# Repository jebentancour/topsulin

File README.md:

# Topsulin

## Software

### BLE Services and Characteristics

|GATT Services |GATT Characteristics            |Description                              |
|--------------|--------------------------------|-----------------------------------------|
|**Glucose**   |0x1808                          |Servicio estándar para glucómetros       |
|0x2A18        |**Glucose Measurement**         |Valores de glucemia                      |
|0x2A34        |**Glucose Measurement Context** |Información adicional (CHO e insulina)   |
|0x2A51        |**Glucose Feature**             |Información sobre features soportadas    |
|0x2A52        |**Record Access Control Point** |Punto de control de acceso del registro  |
|**Topsulin**  |0xF65D                          |Servicio específico de Topsulin          |
|0xF65E        |**Configuration**               |Configuración de preferencias de usuario |
|0xF65F        |**Name**                        |Nombre para mostrar                      |
|0xF660        |**Time**                        |Fecha y hora                             |
|0xF661        |**Calculator**                  |Parámetros para el calculador de bolos   |
|0xF662        |**Insulin**                     |Tipo, capacidad y cantidad restante      |
|0xF663        |**Device**                      |Información sobre el dispositivo         |

Base UUID para Topsulin Services y Characteristics 0x3419-XXXX-1505-31A7-EC4D-449B-0752-1104

#### Glucose Service

Según el servicio estándar [Glucose Service Specification](https://www.bluetooth.com/specifications/gatt/viewer?attributeXmlFile=org.bluetooth.service.glucose.xml)

Definimos que 1 U de insulina se representa como 10 ml.

```c
/**@brief Glucose feature */
#define BLE_GLS_FEATURE_LOW_BATT                       0x0001  /**< Low Battery Detection During Measurement Supported */
#define BLE_GLS_FEATURE_MALFUNC                        0x0002  /**< Sensor Malfunction Detection Supported */
#define BLE_GLS_FEATURE_SAMPLE_SIZE                    0x0004  /**< Sensor Sample Size Supported */
#define BLE_GLS_FEATURE_INSERT_ERR                     0x0008  /**< Sensor Strip Insertion Error Detection Supported */
#define BLE_GLS_FEATURE_TYPE_ERR                       0x0010  /**< Sensor Strip Type Error Detection Supported */
#define BLE_GLS_FEATURE_RES_HIGH_LOW                   0x0020  /**< Sensor Result High-Low Detection Supported */
#define BLE_GLS_FEATURE_TEMP_HIGH_LOW                  0x0040  /**< Sensor Temperature High-Low Detection Supported */
#define BLE_GLS_FEATURE_READ_INT                       0x0080  /**< Sensor Read Interrupt Detection Supported */
#define BLE_GLS_FEATURE_GENERAL_FAULT                  0x0100  /**< General Device Fault Supported */
#define BLE_GLS_FEATURE_TIME_FAULT                     0x0200  /**< Time Fault Supported */
#define BLE_GLS_FEATURE_MULTI_BOND                     0x0400  /**< Multiple Bond Supported */

/**@brief Glucose measurement flags */
#define BLE_GLS_MEAS_FLAG_TIME_OFFSET                  0x01    /**< Time Offset Present */
#define BLE_GLS_MEAS_FLAG_CONC_TYPE_LOC                0x02    /**< Glucose Concentration, Type, and Sample Location Present */
#define BLE_GLS_MEAS_FLAG_UNITS_KG_L                   0x00    /**< Glucose Concentration Units kg/L */
#define BLE_GLS_MEAS_FLAG_UNITS_MOL_L                  0x04    /**< Glucose Concentration Units mol/L */
#define BLE_GLS_MEAS_FLAG_SENSOR_STATUS                0x08    /**< Sensor Status Annunciation Present */
#define BLE_GLS_MEAS_FLAG_CONTEXT_INFO                 0x10    /**< Context Information Follows */

/**@brief Glucose measurement type */
#define BLE_GLS_MEAS_TYPE_CAP_BLOOD                    1       /**< Capillary whole blood */
#define BLE_GLS_MEAS_TYPE_CAP_PLASMA                   2       /**< Capillary plasma */
#define BLE_GLS_MEAS_TYPE_VEN_BLOOD                    3       /**< Venous whole blood */
#define BLE_GLS_MEAS_TYPE_VEN_PLASMA                   4       /**< Venous plasma */
#define BLE_GLS_MEAS_TYPE_ART_BLOOD                    5       /**< Arterial whole blood */
#define BLE_GLS_MEAS_TYPE_ART_PLASMA                   6       /**< Arterial plasma */
#define BLE_GLS_MEAS_TYPE_UNDET_BLOOD                  7       /**< Undetermined whole blood */
#define BLE_GLS_MEAS_TYPE_UNDET_PLASMA                 8       /**< Undetermined plasma */
#define BLE_GLS_MEAS_TYPE_FLUID                        9       /**< Interstitial fluid (ISF) */
#define BLE_GLS_MEAS_TYPE_CONTROL                      10      /**< Control solution */

/**@brief Glucose measurement location */
#define BLE_GLS_MEAS_LOC_FINGER                        1       /**< Finger */
#define BLE_GLS_MEAS_LOC_AST                           2       /**< Alternate Site Test (AST) */
#define BLE_GLS_MEAS_LOC_EAR                           3       /**< Earlobe */
#define BLE_GLS_MEAS_LOC_CONTROL                       4       /**< Control solution */
#define BLE_GLS_MEAS_LOC_NOT_AVAIL                     15      /**< Sample Location value not available */

/**@brief Glucose sensor status annunciation */
#define BLE_GLS_MEAS_STATUS_BATT_LOW                   0x0001  /**< Device battery low at time of measurement */
#define BLE_GLS_MEAS_STATUS_SENSOR_FAULT               0x0002  /**< Sensor malfunction or faulting at time of measurement */
#define BLE_GLS_MEAS_STATUS_SAMPLE_SIZE                0x0004  /**< Sample size for blood or control solution insufficient at time of measurement */
#define BLE_GLS_MEAS_STATUS_STRIP_INSERT               0x0008  /**< Strip insertion error */
#define BLE_GLS_MEAS_STATUS_STRIP_TYPE                 0x0010  /**< Strip type incorrect for device */
#define BLE_GLS_MEAS_STATUS_RESULT_HIGH                0x0020  /**< Sensor result higher than the device can process */
#define BLE_GLS_MEAS_STATUS_RESULT_LOW                 0x0040  /**< Sensor result lower than the device can process */
#define BLE_GLS_MEAS_STATUS_TEMP_HIGH                  0x0080  /**< Sensor temperature too high for valid test/result at time of measurement */
#define BLE_GLS_MEAS_STATUS_TEMP_LOW                   0x0100  /**< Sensor temperature too low for valid test/result at time of measurement */
#define BLE_GLS_MEAS_STATUS_STRIP_PULL                 0x0200  /**< Sensor read interrupted because strip was pulled too soon at time of measurement */
#define BLE_GLS_MEAS_STATUS_GENERAL_FAULT              0x0400  /**< General device fault has occurred in the sensor */
#define BLE_GLS_MEAS_STATUS_TIME_FAULT                 0x0800  /**< Time fault has occurred in the sensor and time may be inaccurate */

/**@brief Glucose measurement context flags */
#define BLE_GLS_CONTEXT_FLAG_CARB                      0x01    /**< Carbohydrate id and carbohydrate present */
#define BLE_GLS_CONTEXT_FLAG_MEAL                      0x02    /**< Meal present */
#define BLE_GLS_CONTEXT_FLAG_TESTER                    0x04    /**< Tester-health present */
#define BLE_GLS_CONTEXT_FLAG_EXERCISE                  0x08    /**< Exercise duration and exercise intensity present */
#define BLE_GLS_CONTEXT_FLAG_MED                       0x10    /**< Medication ID and medication present */
#define BLE_GLS_CONTEXT_FLAG_MED_KG                    0x00    /**< Medication value units, kilograms */
#define BLE_GLS_CONTEXT_FLAG_MED_L                     0x20    /**< Medication value units, liters */
#define BLE_GLS_CONTEXT_FLAG_HBA1C                     0x40    /**< Hba1c present */
#define BLE_GLS_CONTEXT_FLAG_EXT                       0x80    /**< Extended flags present */

/**@brief Glucose measurement context carbohydrate ID */
#define BLE_GLS_CONTEXT_CARB_BREAKFAST                 1       /**< Breakfast */
#define BLE_GLS_CONTEXT_CARB_LUNCH                     2       /**< Lunch */
#define BLE_GLS_CONTEXT_CARB_DINNER                    3       /**< Dinner */
#define BLE_GLS_CONTEXT_CARB_SNACK                     4       /**< Snack */
#define BLE_GLS_CONTEXT_CARB_DRINK                     5       /**< Drink */
#define BLE_GLS_CONTEXT_CARB_SUPPER                    6       /**< Supper */
#define BLE_GLS_CONTEXT_CARB_BRUNCH                    7       /**< Brunch */

/**@brief Glucose measurement context meal */
#define BLE_GLS_CONTEXT_MEAL_PREPRANDIAL               1       /**< Preprandial (before meal) */
#define BLE_GLS_CONTEXT_MEAL_POSTPRANDIAL              2       /**< Postprandial (after meal) */
#define BLE_GLS_CONTEXT_MEAL_FASTING                   3       /**< Fasting */
#define BLE_GLS_CONTEXT_MEAL_CASUAL                    4       /**< Casual (snacks, drinks, etc.) */
#define BLE_GLS_CONTEXT_MEAL_BEDTIME                   5       /**< Bedtime */

/**@brief Glucose measurement context tester */
#define BLE_GLS_CONTEXT_TESTER_SELF                    1       /**< Self */
#define BLE_GLS_CONTEXT_TESTER_PRO                     2       /**< Health care professional */
#define BLE_GLS_CONTEXT_TESTER_LAB                     3       /**< Lab test */
#define BLE_GLS_CONTEXT_TESTER_NOT_AVAIL               15      /**< Tester value not available */

/**@brief Glucose measurement context health */
#define BLE_GLS_CONTEXT_HEALTH_MINOR                   1       /**< Minor health issues */
#define BLE_GLS_CONTEXT_HEALTH_MAJOR                   2       /**< Major health issues */
#define BLE_GLS_CONTEXT_HEALTH_MENSES                  3       /**< During menses */
#define BLE_GLS_CONTEXT_HEALTH_STRESS                  4       /**< Under stress */
#define BLE_GLS_CONTEXT_HEALTH_NONE                    5       /**< No health issues */
#define BLE_GLS_CONTEXT_HEALTH_NOT_AVAIL               15      /**< Health value not available */

/**@brief Glucose measurement context medication ID */
#define BLE_GLS_CONTEXT_MED_RAPID                      1       /**< Rapid acting insulin */
#define BLE_GLS_CONTEXT_MED_SHORT                      2       /**< Short acting insulin */
#define BLE_GLS_CONTEXT_MED_INTERMED                   3       /**< Intermediate acting insulin */
#define BLE_GLS_CONTEXT_MED_LONG                       4       /**< Long acting insulin */
#define BLE_GLS_CONTEXT_MED_PREMIX                     5       /**< Pre-mixed insulin */

/**@brief SFLOAT format (IEEE-11073 16-bit FLOAT, meaning 4 bits for exponent (base 10) and 12 bits mantissa) */
typedef struct
{
  int8_t exponent;                                             /**< Base 10 exponent, should be using only 4 bits */
  int16_t mantissa;                                            /**< Mantissa, should be using only 12 bits */
} sfloat_t;
```

Los enteros de 16 bits se codifican de manera que el byte más alto va primero. El número 250 en hexadecimal es 0x00FA, sin embargo en BLE se lee el byte 0xFA00.

El sfloat se usa para guardar un número con coma en 16 bits, los primeros 12 bits son la mantisa y los otros 4 el exponente.

```c
uint16_t encode_sfloat(sfloat_t sf)
{
    uint16_t dec;
    dec = ((sf.exponent << 12) & 0xF000) | ((sf.mantissa <<  0) & 0x0FFF);
    return dec;
}

sfloat_t decode_sfloat(uint16_t u)
{
    sfloat_t sf;
    sf.exponent = (u & 0xF000) >> 12;
    sf.mantissa = (u & 0x0FFF) >> 0;
    return sf;
}
```

#### Topsulin Service

[Characteristic Format Types](https://www.bluetooth.com/specifications/assigned-numbers/format-types)

|Characteristic                                      |Format |Value                              |Default                   |
|----------------------------------------------------|-------|-----------------------------------|--------------------------|
|**Configuration**                                   |       |                                   |                          |
|Registro de glucemia                                |bit0   |0 No, 1 Si                         |Si                        |
|Registro de insulina                                |bit1   |0 No, 1 Si                         |Si                        |
|Registro de CHO                                     |bit2   |0 No, 1 Si                         |Si                        |
|Invertir los colores de la pantalla                 |bit3   |0 Fondo blanco, 1 Fondo negro      |Fondo blanco              |
|Unidades de glucemia                                |bit4   |0 kg/L, 1 mol/L                    |kg/L                      |
|Calculador de bolo                                  |bit5   |0 Desactivado, 1 Activado          |Desactivado               |
|Orientación de pantalla                             |bit6   |0 Diestro, 1 Zurdo                 |Diestro                   |
|Unidades de CHO                                     |bit7   |0 CHO en g, 1 CHO en porciones     |CHO en g                  |
|Equivalencia entre gramos y porciones               |uint16 |Peso en g de una porción           |250 g                     |
|Incremento de CHO                                   |uint8  |Paso de ingreso de CHO en g        |5 g                       |
|Incremento de insulina                              |uint8  |Paso de ingreso de insulina x10    |10 (equivale a 1U)        |
|**Name**                                            |       |                                   |                          |
|Nombre para mostrar                                 |uint8  |String de largo máximo 20 UTF-8    |Glucosee                  |
|**Time**                                            |       |                                   |                          |
|Hora y fecha del dispositivo                        |time   |[Time Characteristic](https://www.bluetooth.com/specifications/gatt/viewer?attributeXmlFile=org.bluetooth.characteristic.date_time.xml) |01/01/19 12:00:00 |
|**Calculator**                                      |       |                                   |                          |
|Nivel bajo                                          |sfloat |Nivel de glucemia baja en kg/L     |90x10^-5 kg/L             |
|Nivel alto                                          |sfloat |Nivel de glucemia alta en kg/L     |150x10^-5 kg/L            |
|Sensibilidad                                        |uint16 |Cada cuántos CHO en g incremento insulina |15 g               |
|Corrección de hiperglucemia                         |sfloat |Cada cuántos kg/L de hiper incremento insulina |50x10^-5 kg/L |
|**Insulin**                                         |       |                                   |                          |
|Tipo de insulina                                    |uint8  |Medication ID from Glucose Service |BLE_GLS_CONTEXT_MED_RAPID |
|Capacidad de la lapicera                            |uint16 |U de insulina en una lapicera nueva|300 U                     |
|Capacidad restante de la lapicera                   |uint16 |U de insulina restantes            |120 U                     |
|Comienzo de acción                                  |uint16 |En minutos                         |30 m                      |
|Acción máxima                                       |uint16 |En minutos                         |120 m                     |
|Duración de la acción                               |uint16 |En minutos                         |360 m                     |
|**Device**                                          |       |                                   |                          |
|Firmware                                            |uint8  |Versión de firmware                |1                         |
|Serial Number                                       |uint16 |Número de serie                    |1                         |
|Battery                                             |uint16 |Voltaje de la batería en mV        |Cerca de 3300 mV          |

## Board

## Encoder

|nRF pin|Use  |
|-------|-----|
|01     |A    |
|00     |B    |
|30     |SW   |

## Display

|nRF pin|Use  |
|-------|-----|
|21     |MOSI |
|22     |CLK  |
|23     |CS   |
|24     |DC   |
|25     |RST  |
|28     |BUSY |

## SoC

SoC [nRF51822](https://www.nordicsemi.com/eng/nordic/download_resource/62726/14/39584073/13358) QFACA10 (256kB flash, 32 kB RAM)

[INFOCENTER](http://infocenter.nordicsemi.com)

|ID |Base address |Peripheral  |Instance    |Description                                  |Used by           |
|---|-------------|------------|------------|---------------------------------------------|------------------|
|0  |0x40000000   |POWER       |POWER       |Power Control.                               |SoftDevice        |
|0  |0x40000000   |CLOCK       |CLOCK       |Clock Control.                               |SoftDevice        |
|0  |0x40000000   |MPU         |MPU         |Memory Protection Unit.                      |SoftDevice        |
|1  |0x40001000   |RADIO       |RADIO       |2.4 GHz Radio.                               |SoftDevice        |
|2  |0x40002000   |UART        |UART0       |Universal Asynchronous Receiver/Transmitter. |                  |
|3  |0x40003000   |SPI         |SPI0        |SPI Master.                                  |EPD (SPI)         |
|3  |0x40003000   |TWI         |TWI0        |I2C compatible Two-Wire Interface 0.         |EPD (SPI)         |
|4  |0x40004000   |SPIS        |SPIS1       |SPI Slave.                                   |                  |
|4  |0x40004000   |SPI         |SPI1        |SPI Master.                                  |                  |
|4  |0x40004000   |TWI         |TWI1        |I2C compatible Two-Wire Interface 1.         |                  |
|6  |0x40006000   |GPIOTE      |GPIOTE      |GPIO Task and Events.                        |                  |
|7  |0x40007000   |ADC         |ADC         |Analog to Digital Converter.                 |Battery           |
|8  |0x40008000   |TIMER       |TIMER0      |Timer/Counter 0.                             |SoftDevice        |
|9  |0x40009000   |TIMER       |TIMER1      |Timer/Counter 1.                             |                  |
|10 |0x4000A000   |TIMER       |TIMER2      |Timer/Counter 2.                             |                  |
|11 |0x4000B000   |RTC         |RTC0        |Real Time Counter 0.                         |SoftDevice        |
|12 |0x4000C000   |TEMP        |TEMP        |Temperature Sensor.                          |SoftDevice        |
|13 |0x4000D000   |RNG         |RNG         |Random Number Generator.                     |SoftDevice        |
|14 |0x4000E000   |ECB         |ECB         |Crypto AES ECB.                              |SoftDevice        |
|15 |0x4000F000   |CCM         |CCM         |AES Crypto CCM.                              |SoftDevice        |
|15 |0x4000F000   |AAR         |AAR         |Accelerated Address Resolver.                |SoftDevice        |
|16 |0x40010000   |WDT         |WDT         |Watchdog Timer.                              |                  |
|17 |0x40011000   |RTC         |RTC1        |Real Time Counter 1.                         |Timer library     |
|18 |0x40012000   |QDEC        |QDEC        |Quadrature Decoder.                          |Encoder           |
|19 |0x40013000   |LPCOMP      |LPCOMP      |Low Power Comparator.                        |                  |
|20 |0x40014000   |SWI         |SWI0        |Software interrupt.                          |Timer library     |
|21 |0x40015000   |SWI         |SWI1        |Software interrupt.                          |SoftDevice        |
|22 |0x40016000   |SWI         |SWI2        |Software interrupt                           |SoftDevice        |
|23 |0x40017000   |SWI         |SWI3        |Software interrupt.                          |                  |
|24 |0x40018000   |SWI         |SWI4        |Software interrupt.                          |SoftDevice        |
|25 |0x40019000   |SWI         |SWI5        |Software interrupt.                          |SoftDevice        |
|30 |0x4001E000   |NVMC        |NVMC        |Non-Volatile Memory Controller.              |SoftDevice        |
|31 |0x4001F000   |PPI         |PPI         |Programmable Peripheral Interconnect.        |                  |
|NA |0x50000000   |GPIO        |GPIO        |General Purpose Input and Output.            |Gpio              |
|NA |0x10000000   |FICR        |FICR        |Factory Information Configuration Registers. |SoftDevice        |
|NA |0x10001000   |UICR        |UICR        |User Information Configuration Registers.    |SoftDevice        |

## EPD

[Image file to embedded C/C++ code](https://digole.com/tools/PicturetoC_Hex_converter.php)

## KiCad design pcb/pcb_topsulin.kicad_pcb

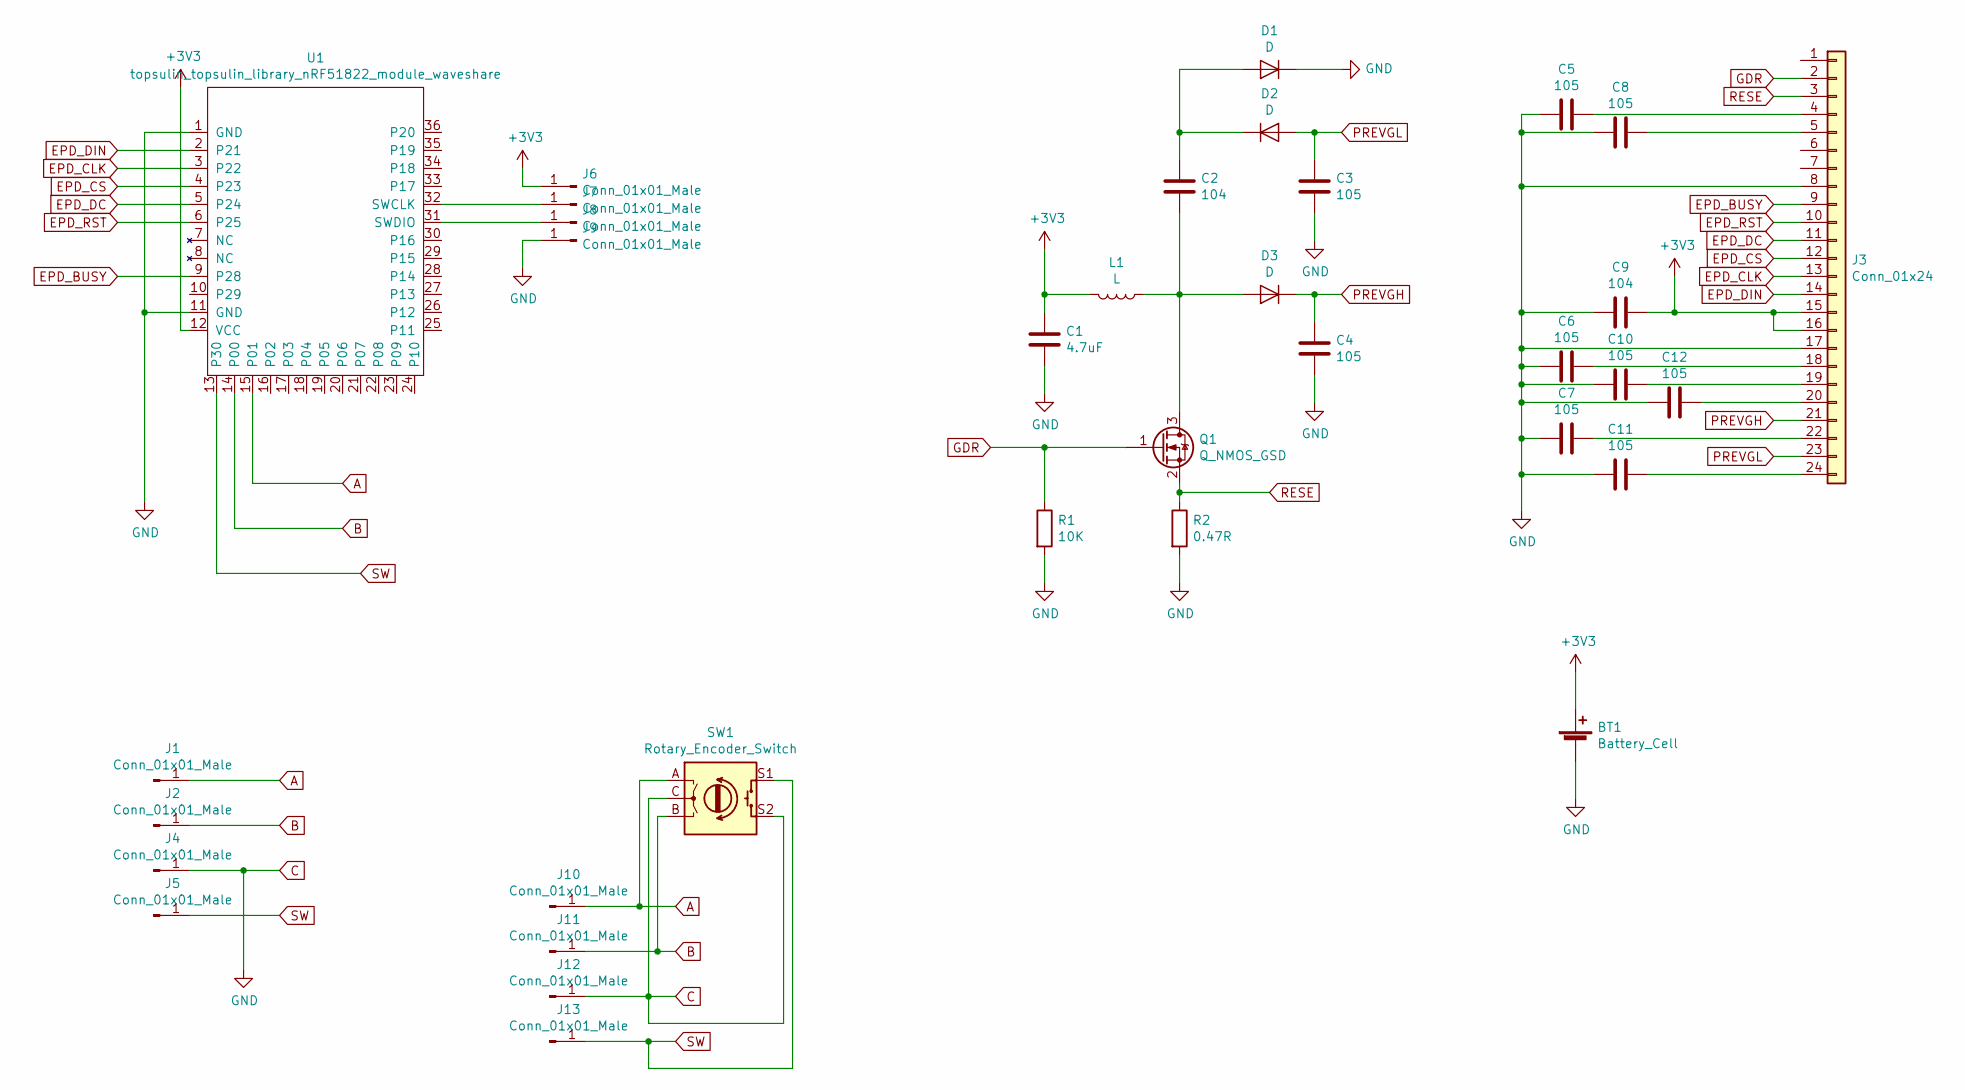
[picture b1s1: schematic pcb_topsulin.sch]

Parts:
BT1: Battery_Cell; BatteryHolder_Keystone_1058_1x2032
C1: 4.7uF; C_0603_1608Metric
C2, C9: 104; C_0603_1608Metric
C3, C4, C5, C6, C7, C8, C10, C11, C12: 105; C_0603_1608Metric
D1, D2, D3: D; D_SOD-123
J1, J2, J4, J5, J10, J11, J12, J13: Conn_01x01_Male; TestPoint_Pad_2.0x2.0mm
J3: Conn_01x24; e-paper-2in13-flex
J6, J7, J8, J9: Conn_01x01_Male; TestPoint_Pad_1.0x1.0mm
L1: L; L_0805_2012Metric
Q1: Q_NMOS_GSD; SOT-23
R1: 10K; R_0603_1608Metric
R2: 0.47R; R_0603_1608Metric
SW1: Rotary_Encoder_Switch; RotaryEncoder_Alps_EC12E-Switch_Vertical_H20mm
U1: topsulin_topsulin_library_nRF51822_module_wavesha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; nRF51822_module_waveshare_footprint

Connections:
+3V3: BT1.1 (+), C1.1, C9.1, J3.15, J3.16, J6.1, L1.2, U1.12 (VCC)
A: J1.1, J10.1, SW1.A, U1.15 (P01)
B: J2.1, J11.1, SW1.B, U1.14 (P00)
C: BT1.2 (-), C1.2, C3.2, C4.2, C5.2, C6.2, C7.2, C8.2, C9.2, C10.2, C11.2, C12.2, D1.1 (K), J3.8, J3.17, J4.1, J9.1, J12.1, R1.2, R2.2, SW1.C, SW1.S2, U1.1 (GND), U1.11 (GND)
EPD_BUSY: J3.9, U1.9 (P28)
EPD_CLK: J3.13, U1.3 (P22)
EPD_CS: J3.12, U1.4 (P23)
EPD_DC: J3.11, U1.5 (P24)
EPD_DIN: J3.14, U1.2 (P21)
EPD_RST: J3.10, U1.6 (P25)
GDR: J3.2, Q1.1 (G), R1.1
unnamed: C2.1, D1.2 (A), D2.1 (K)
unnamed: C2.2, D3.2 (A), L1.1, Q1.3 (D)
unnamed: C5.1, J3.4
unnamed: C6.1, J3.18
unnamed: C7.1, J3.22
unnamed: C8.1, J3.5
unnamed: C10.1, J3.19
unnamed: C11.1, J3.24
unnamed: C12.1, J3.20
unnamed: J7.1, U1.32 (SWCLK)
unnamed: J8.1, U1.31 (SWDIO)
PREVGH: C4.1, D3.1 (K), J3.21
PREVGL: C3.1, D2.2 (A), J3.23
RESE: J3.3, Q1.2 (S), R2.1
SW: J5.1, J13.1, SW1.S1, U1.13 (P30)

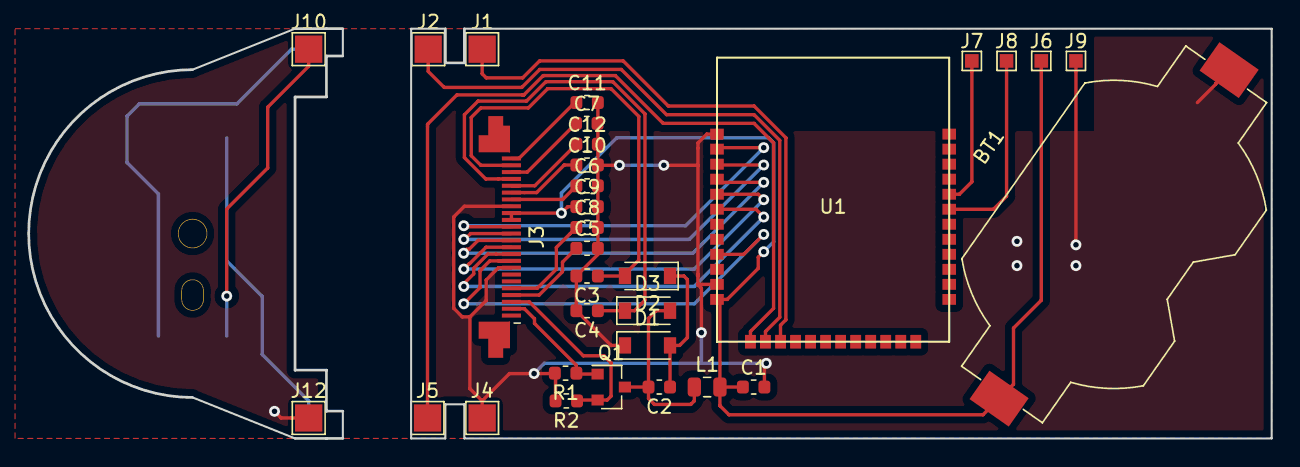
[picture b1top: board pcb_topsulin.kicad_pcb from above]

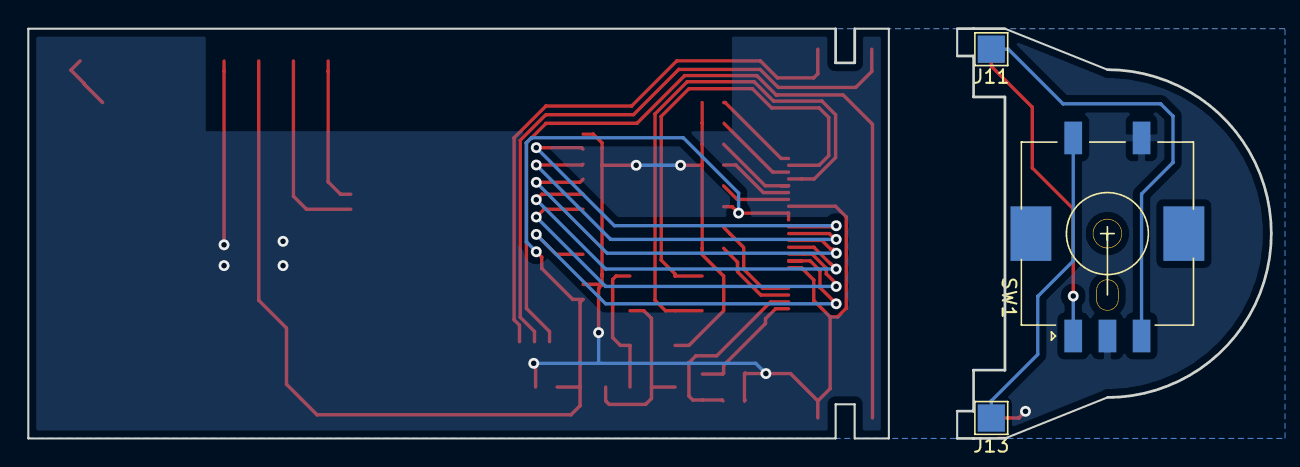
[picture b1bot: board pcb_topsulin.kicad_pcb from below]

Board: 2 copper layers, 63.0 x 30.0 mm, 35 parts (3 on the bottom side), 26 nets.

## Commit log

2018-07-22 Initial IAR project
2018-07-24 Display library working
2018-10-05 IAR limit
2018-10-11 Make working
2018-10-12 Nordic GLS
2018-10-15 Custom Service
2018-10-15 Glucose context support
2018-10-17 Display string support
2018-10-19 Encoder support
2018-10-23 Maker Fair firmware
2018-10-25 Battery support
2018-11-19 Waveshare module
2018-11-19 EPD library
2018-11-26 Add BLE services
2018-12-11 Initial config manager
2018-12-12 Name characteristic
2018-12-12 Insulin characteristic
2018-12-21 BLE services complete
2019-01-02 Config manager update
2019-01-02 EPD working
2019-01-22 Initial beta hardware
2019-01-29 GPIO long press
2019-02-01 Sate v1
2019-02-04 State v2
2019-02-11 Encoder update
2019-02-11 State v3
2019-03-12 Encoder fix, icon update and cho incremet 5
2019-04-02 Incons update
2019-04-03 Text centering
2019-04-04 Long press exit
2019-04-04 Insulin change indication
2019-04-05 Flip support
2019-04-05 Calculator on/off
2019-04-09 Memory full warning
2019-04-09 Low glu fixes
2019-04-10 Low battery warning
2019-04-11 Bug fix
2019-04-12 Energy management
2019-04-16 Image change
2019-04-24 Button and state
2019-04-26 Sleep time to 60s
2019-05-02 Beta testers
2019-05-06 Switch to linux
2019-05-06 Diferent names
2019-05-08 Bluetooth state
2019-05-09 Show device name
2019-05-09 Variable CHO step
2019-05-09 Show memory
2019-05-09 Screen info update
2019-05-10 Insulin interval
2019-05-23 Insulin centering
2019-06-10 New screen working
2019-06-17 New screen layout
2019-09-13 add pcb
2019-09-15 state begin fix
2019-09-24 initial screen complete
2019-10-19 calc and battery icons
2019-10-20 dark mode
2019-10-23 calc data
2019-10-30 calc icon
2019-11-04 zurdo
2019-11-09 long long click
2019-11-11 it works
2019-11-15 it works 2
2019-11-27 CHO start from zero
